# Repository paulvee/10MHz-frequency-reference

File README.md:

# 10MHz-frequency-reference
This project details a 10MHz frequency reference or a master clock
I updated a few footprints with better dimensions and added more partnumbers.
The current version is now V1.1b

More information can be found on my Blog here:
https://www.paulvdiyblogs.net/2023/07/building-10mhz-master-clock.html

If you want to order PCB's, have a look at my Shared Project here: 
https://www.pcbway.com/project/shareproject/10MHz_frequency_reference_1_of_2_8cf54ec4.html
https://www.pcbway.com/project/shareproject/10MHz_frequency_reference_2_of_2_f23ccc53.html

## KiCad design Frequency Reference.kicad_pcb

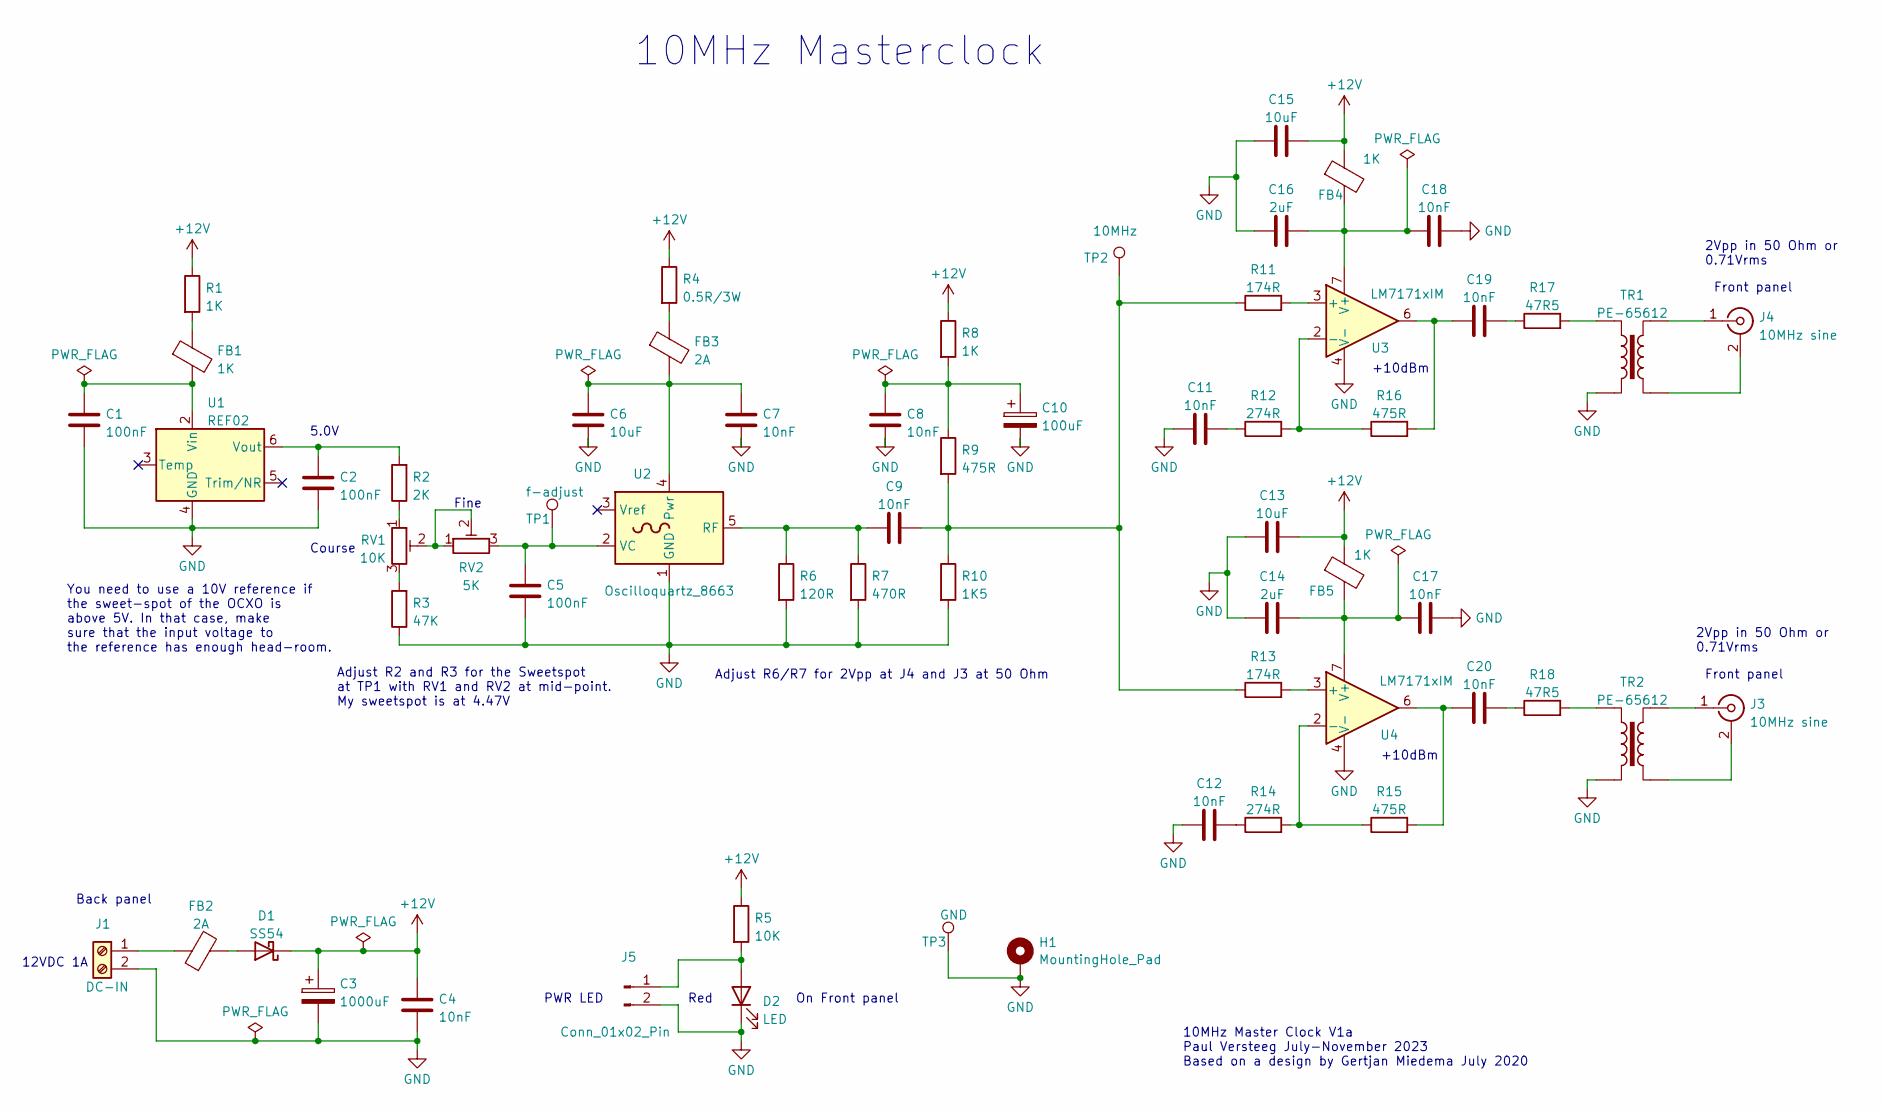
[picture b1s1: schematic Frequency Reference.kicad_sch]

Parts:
C1, C2, C5: 100nF; C_0805_2012Metric_Pad1.18x1.45mm_HandSolder
C3: 1000uF; CP_Radial_D8.0mm_P5.00mm
C4, C7, C8, C9, C11, C12, C17, C18, C19, C20: 10nF; C_0805_2012Metric_Pad1.18x1.45mm_HandSolder
C6, C13, C15: 10uF; C_0805_2012Metric_Pad1.18x1.45mm_HandSolder
C10: 100uF; CP_Radial_D6.3mm_P2.50mm
C14, C16: 2uF; C_0805_2012Metric_Pad1.18x1.45mm_HandSolder
D1: SS54; D_1210_3225Metric_Pad1.42x2.65mm_HandSolder
D2: LED
FB1, FB4, FB5: 1K; L_0805_2012Metric_Pad1.05x1.20mm_HandSolder
FB2: 2A; L_Axial_L7.0mm_D3.3mm_P2.54mm_Vertical_Fastron_MICC
FB3: 2A; L_0805_2012Metric_Pad1.05x1.20mm_HandSolder
H1: MountingHole_Pad; MountingHole_3.2mm_M3_DIN965_Pad_TopBottom
J1: DC-IN; TerminalBlock_Altech_AK300-2_P5.00mm
J3, J4: 10MHz sine; SMA_Samtec_SMA-J-P-X-ST-EM1_EdgeMount
J5: Conn_01x02_Pin; PinHeader_1x02_P2.54mm_Vertical
R1, R8: 1K; R_0805_2012Metric_Pad1.20x1.40mm_HandSolder
R2: 2K; R_0805_2012Metric_Pad1.20x1.40mm_HandSolder
R3: 47K; R_0805_2012Metric_Pad1.20x1.40mm_HandSolder
R4: 0.5R/3W; R_2512_6332Metric_Pad1.40x3.35mm_HandSolder
R5: 10K; R_0805_2012Metric_Pad1.20x1.40mm_HandSolder
R6: 120R; R_0805_2012Metric_Pad1.20x1.40mm_HandSolder
R7: 470R; R_0805_2012Metric_Pad1.20x1.40mm_HandSolder
R9, R15, R16: 475R; R_0805_2012Metric_Pad1.20x1.40mm_HandSolder
R10: 1K5; R_0805_2012Metric_Pad1.20x1.40mm_HandSolder
R11, R13: 174R; R_0805_2012Metric_Pad1.20x1.40mm_HandSolder
R12, R14: 274R; R_0805_2012Metric_Pad1.20x1.40mm_HandSolder
R17, R18: 47R5; R_0805_2012Metric_Pad1.20x1.40mm_HandSolder
RV1: 10K; Potentiometer_Bourns_3053P_Horizontal
RV2: 5K; Potentiometer_Bourns_3053P_Horizontal
TP1: f-adjust; TestPoint_Keystone_5005-5009_Compact
TP2: 10MHz; TestPoint_Keystone_5005-5009_Compact
TP3: GND; TestPoint_Keystone_5005-5009_Compact
TR1, TR2: PE-65612
U1: REF02; SOIC-8_3.9x4.9mm_P1.27mm
U2: Oscilloquartz_8663
U3, U4: LM7171xIM; SOIC-8_3.9x4.9mm_P1.27mm

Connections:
GND: C1.2, C2.2, C3.2, C4.2, C5.2, C6.2, C7.2, C8.2, C10.2, C11.1, C12.1, C13.1, C14.1, C15.1, C16.1, C17.2, C18.2, D2.1 (K), H1.1, J1.2, J5.2, R3.1, R6.2, R7.2, R10.2, TP3.1, TR1.2, TR2.2, U1.4 (GND), U2.1 (GND), U3.4 (V-), U4.4 (V-); also elsewhere on the board
unnamed: C9.2, R9.2, R10.1, R11.1, R13.1, TP2.1
unnamed: C8.1, C10.1, R8.2, R9.1
unnamed: C11.2, R12.1
unnamed: C12.2, R14.1
unnamed: C19.1, R16.2, U3.6
unnamed: C19.2, R17.1
unnamed: C20.1, R15.2, U4.6
unnamed: C20.2, R18.1
unnamed: D1.2 (A), FB2.2
unnamed: FB1.1, R1.2
unnamed: FB3.1, R4.2
unnamed: FB2.1, J1.1
unnamed: J3.2 (Ext), TR2.4
unnamed: J3.1 (In), TR2.3
unnamed: J4.2 (Ext), TR1.4
unnamed: J4.1 (In), TR1.3
unnamed: D2.2 (A), J5.1, R5.2
unnamed: R2.1, RV1.1
unnamed: R3.2, RV1.3
unnamed: R17.2, TR1.1
unnamed: R18.2, TR2.1
unnamed: RV1.2, RV2.1, RV2.2
unnamed: C1.1, FB1.2, U1.2 (Vin)
unnamed: C2.1, R2.2, U1.6 (Vout)
unnamed: C6.1, C7.1, FB3.2, U2.4 (Pwr)
unnamed: C9.1, R6.1, R7.1, U2.5 (RF)
unnamed: C5.1, RV2.3, TP1.1, U2.2 (VC)
unnamed: R11.2, U3.3 (+)
unnamed: R12.2, R16.1, U3.2 (-)
unnamed: C16.2, C18.1, FB4.2, U3.7 (V+)
unnamed: R13.2, U4.3 (+)
unnamed: R14.2, R15.1, U4.2 (-)
unnamed: C14.2, C17.1, FB5.2, U4.7 (V+)

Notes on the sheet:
+10dBm
Red
12VDC 1A
Adjust R2 and R3 for the Sweetspot at TP1 with RV1 and RV2 at mid-point. My sweetspot is at 4.47V
2Vpp in 50 Ohm or 0.71Vrms
Front panel
On Front panel
10MHz Master Clock V1a Paul Versteeg July-November 2023 Based on a design by Gertjan Miedema July 2020
Back panel
PWR LED
5.0V
Course
Adjust R6/R7 for 2Vpp at J4 and J3 at 50 Ohm
Fine
10MHz Masterclock
You need to use a 10V reference if the sweet-spot of the OCXO is above 5V. In that case, make sure that the input voltage to the reference has enough head-room.

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
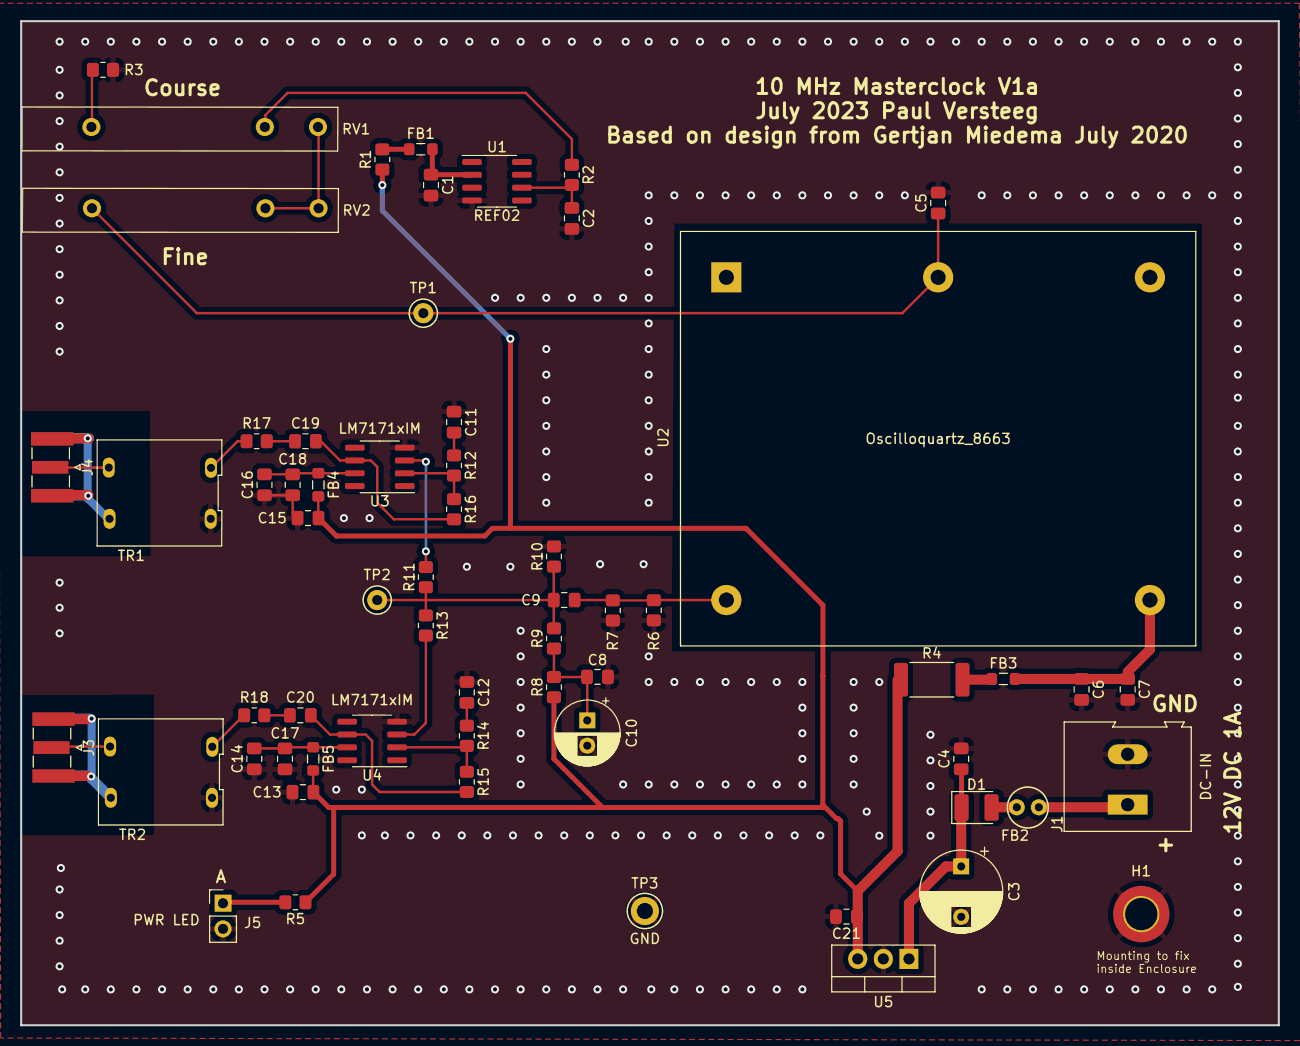
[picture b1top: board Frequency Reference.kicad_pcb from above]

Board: 2 copper layers, 124.7 x 99.6 mm, 62 parts (0 on the bottom side), 36 nets.

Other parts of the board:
C21: 100nF; C_0805_2012Metric_Pad1.18x1.45mm_HandSolder
U5: L7812; TO-220-3_Vertical

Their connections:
GND: C21.2, U5.2 (GND); also elsewhere on the board

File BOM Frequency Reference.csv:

"null,""Sourced"",""Placed"",""References"",""Value"",""Footprint"",""Quantity"""
"1,"""","""",""C4, C7, C8, C9, C11, C12, C17, C18, C19, C20"",""10nF"",""C_0805_2012Metric_Pad1.18x1.45mm_HandSolder"",10"
"2,"""","""",""C1, C2, C5, C21"",""100nF"",""C_0805_2012Metric_Pad1.18x1.45mm_HandSolder"",4"
"3,"""","""",""C6, C13, C15"",""10uF"",""C_0805_2012Metric_Pad1.18x1.45mm_HandSolder"",3"
"4,"""","""",""C14, C16"",""2uF"",""C_0805_2012Metric_Pad1.18x1.45mm_HandSolder"",2"
"5,"""","""",""C3"",""1000uF"",""CP_Radial_D8.0mm_P5.00mm"",1"
"6,"""","""",""C10"",""100uF"",""CP_Radial_D6.3mm_P2.50mm"",1"
"7,"""","""",""R9, R15, R16"",""475R"",""R_0805_2012Metric_Pad1.20x1.40mm_HandSolder"",3"
"8,"""","""",""R1, R8"",""1K"",""R_0805_2012Metric_Pad1.20x1.40mm_HandSolder"",2"
"9,"""","""",""R11, R13"",""174R"",""R_0805_2012Metric_Pad1.20x1.40mm_HandSolder"",2"
"10,"""","""",""R12, R14"",""274R"",""R_0805_2012Metric_Pad1.20x1.40mm_HandSolder"",2"
"11,"""","""",""R17, R18"",""47R5"",""R_0805_2012Metric_Pad1.20x1.40mm_HandSolder"",2"
"12,"""","""",""R2"",""2K"",""R_0805_2012Metric_Pad1.20x1.40mm_HandSolder"",1"
"13,"""","""",""R3"",""47K"",""R_0805_2012Metric_Pad1.20x1.40mm_HandSolder"",1"
"14,"""","""",""R4"",""0.5R/3W"",""R_2512_6332Metric_Pad1.40x3.35mm_HandSolder"",1"
"15,"""","""",""R5"",""10K"",""R_0805_2012Metric_Pad1.20x1.40mm_HandSolder"",1"
"16,"""","""",""R6"",""120R"",""R_0805_2012Metric_Pad1.20x1.40mm_HandSolder"",1"
"17,"""","""",""R7"",""470R"",""R_0805_2012Metric_Pad1.20x1.40mm_HandSolder"",1"
"18,"""","""",""R10"",""1K5"",""R_0805_2012Metric_Pad1.20x1.40mm_HandSolder"",1"
"19,"""","""",""D1"",""SS54"",""D_1210_3225Metric_Pad1.42x2.65mm_HandSolder"",1"
"20,"""","""",""U3, U4"",""LM7171xIM"",""SOIC-8_3.9x4.9mm_P1.27mm"",2"
"21,"""","""",""U1"",""REF02"",""SOIC-8_3.9x4.9mm_P1.27mm"",1"
"22,"""","""",""U2"",""Oscilloquartz_8663"",""Oscilloquartz_8663"",1"
"23,"""","""",""U5"",""L7812"",""TO-220-3_Vertical"",1"
"24,"""","""",""FB1, FB4, FB5"",""1K"",""L_0805_2012Metric_Pad1.05x1.20mm_HandSolder"",3"
"25,"""","""",""TR1, TR2"",""PE-65612"",""PE-65612"",2"
"26,"""","""",""FB2"",""2A"",""L_Axial_L7.0mm_D3.3mm_P2.54mm_Vertical_Fastron_MICC"",1"
"27,"""","""",""FB3"",""2A"",""L_0805_2012Metric_Pad1.05x1.20mm_HandSolder"",1"
"28,"""","""",""H1"",""MountingHole_Pad"",""MountingHole_3.2mm_M3_DIN965_Pad_TopBottom"",1"
"29,"""","""",""RV1"",""10K"",""Potentiometer_Bourns_3053P_Horizontal"",1"
"30,"""","""",""RV2"",""5K"",""Potentiometer_Bourns_3053P_Horizontal"",1"
"31,"""","""",""TP1"",""f-adjust"",""TestPoint_Keystone_5000-5004_Miniature"",1"
"32,"""","""",""TP2"",""10MHz"",""TestPoint_Keystone_5000-5004_Miniature"",1"
"33,"""","""",""TP3"",""GND"",""TestPoint_Keystone_5005-5009_Compact"",1"
"34,"""","""",""J3, J4"",""10MHz sine"",""SMA_Samtec_SMA-J-P-X-ST-EM1_EdgeMount"",2"
"35,"""","""",""J1"",""DC-IN"",""TerminalBlock_Altech_AK300-2_P5.00mm"",1"
"36,"""","""",""J5"",""Conn_01x02_Pin"",""PinHeader_1x02_P2.54mm_Vertical"",1"
